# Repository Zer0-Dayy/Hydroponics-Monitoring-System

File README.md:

# Hydroponics Monitoring System

The [project handover](Project%20Handover/Source%20Code/HANDOVER.md) contains earlier source material for reference.

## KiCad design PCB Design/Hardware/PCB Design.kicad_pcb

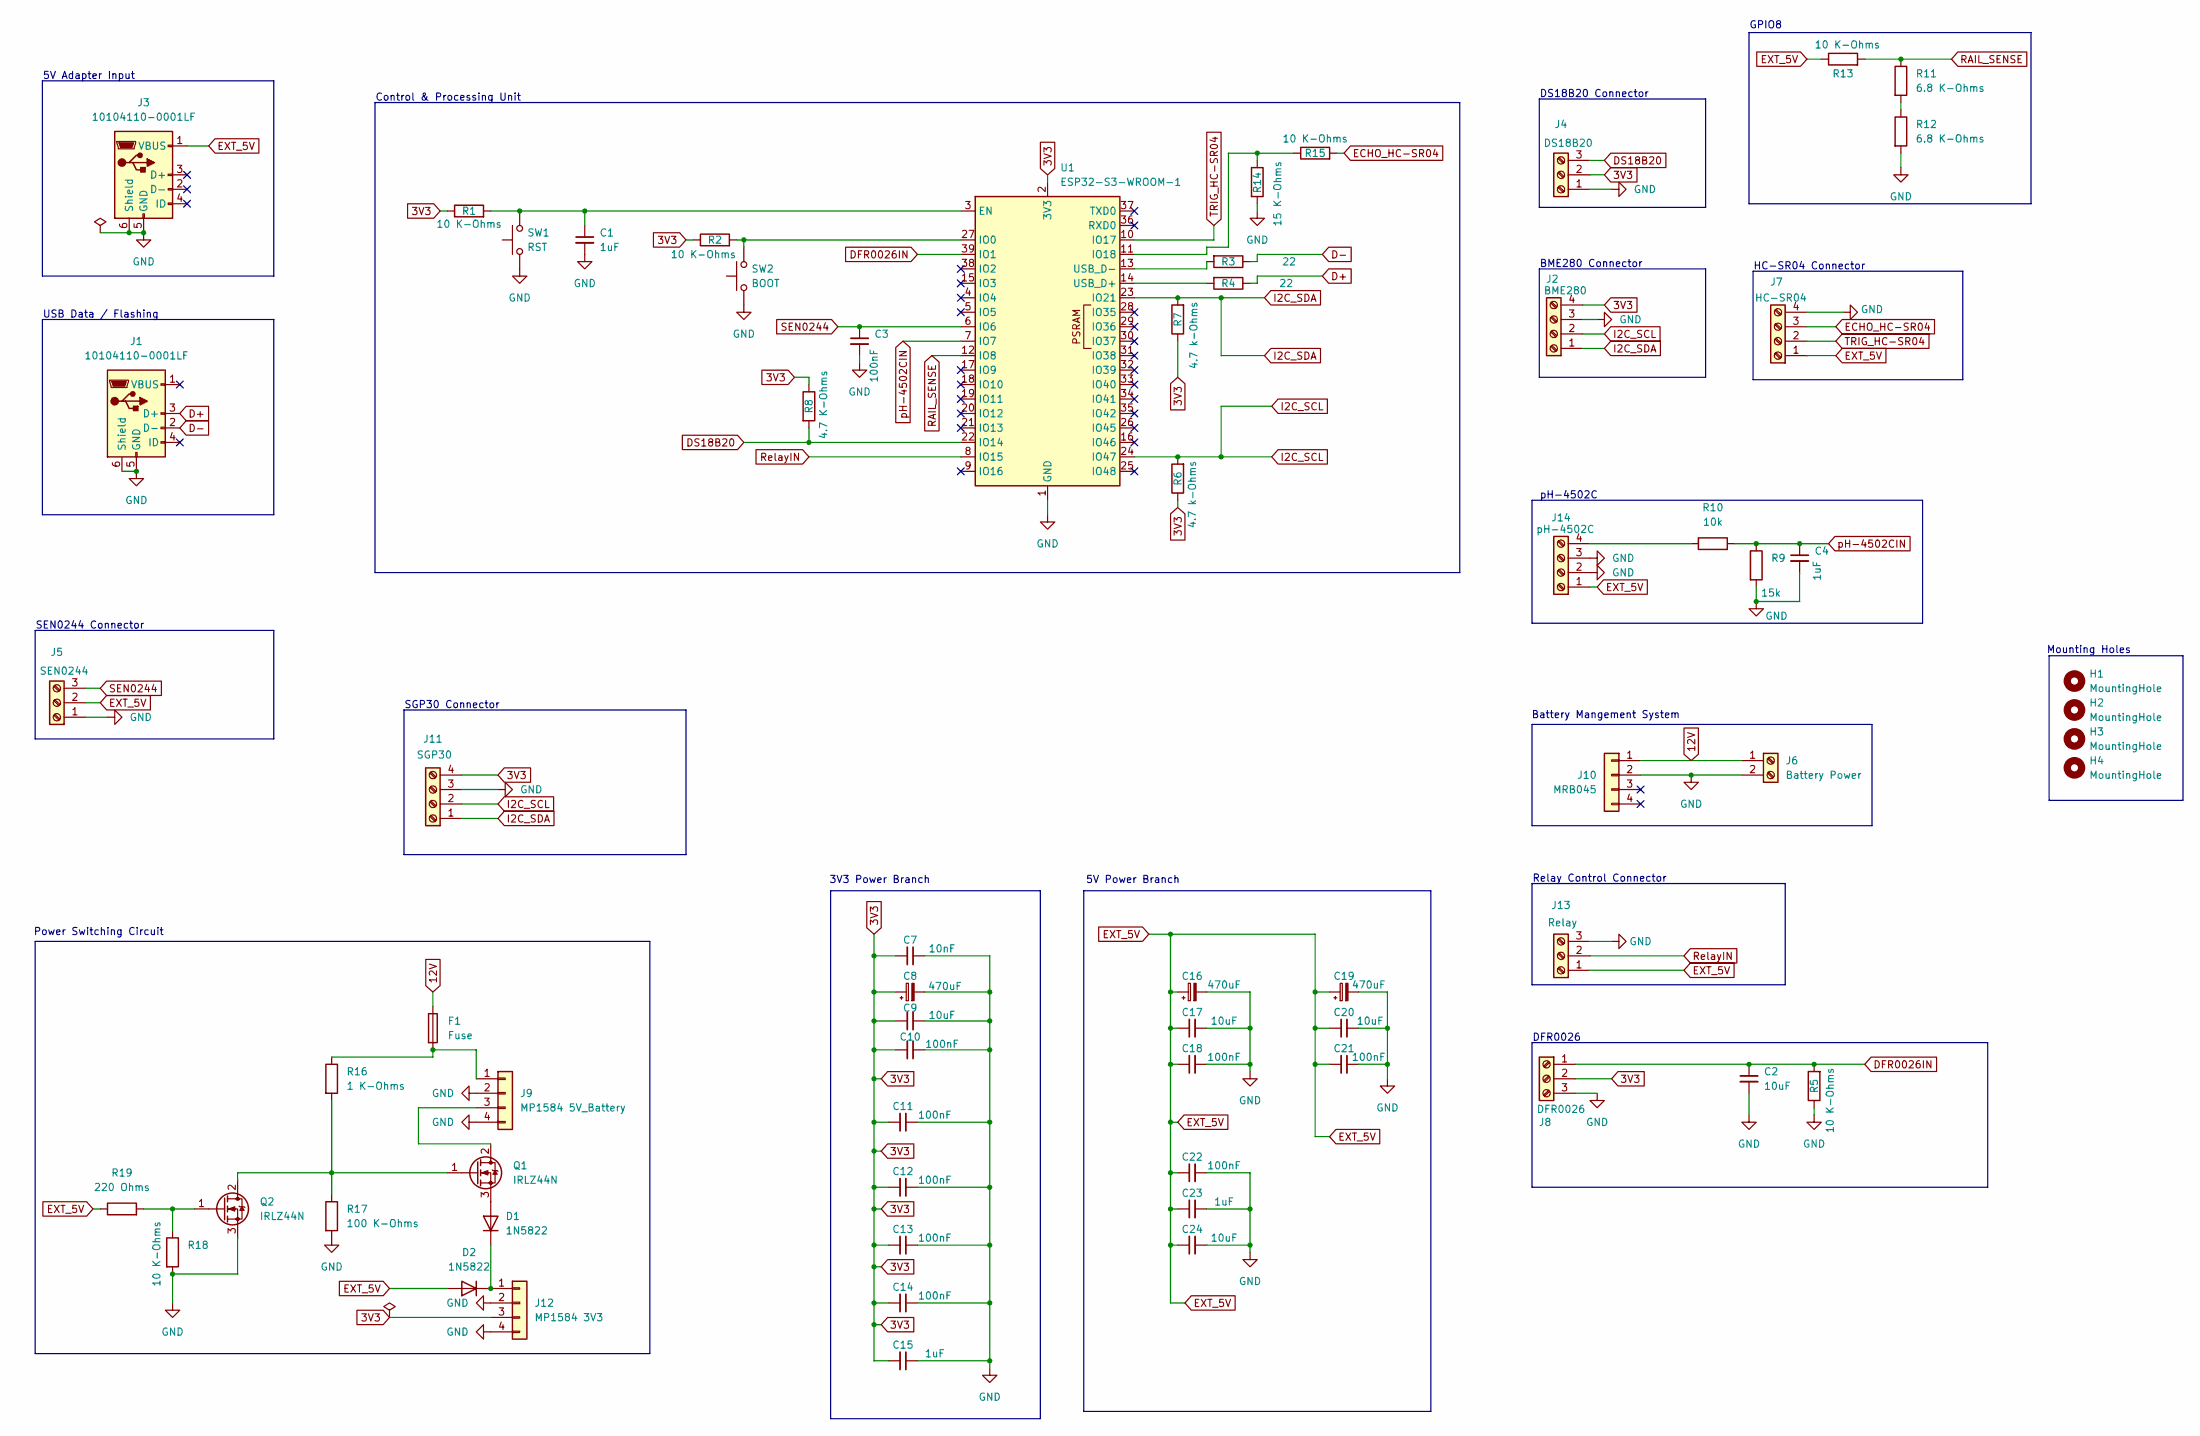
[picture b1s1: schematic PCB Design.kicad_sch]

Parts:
C1: 1uF; C_0402_1005Metric__C1
C2: 10uF; C_0805_2012Metric__C2
C3: 100nF; C_0805_2012Metric_Pad1.18x1.45mm_HandSolder__C3
C4: 1uF; C_0402_1005Metric__C4
C7: 10nF; C_0805_2012Metric__C7
C8: 470uF; CP_Radial_D5.0mm_P2.00mm__C8
C9: 10uF; C_0805_2012Metric__C9
C10: 100nF; C_0805_2012Metric__C10
C11: 100nF; C_0805_2012Metric__C11
C12: 100nF; C_0805_2012Metric__C12
C13: 100nF; C_0805_2012Metric__C13
C14: 100nF; C_0805_2012Metric__C14
C15: 1uF; C_0402_1005Metric__C15
C16: 470uF; CP_Radial_D5.0mm_P2.00mm__C16
C17: 10uF; C_0805_2012Metric__C17
C18: 100nF; C_0805_2012Metric__C18
C19: 470uF; CP_Radial_D5.0mm_P2.00mm__C19
C20: 10uF; C_0805_2012Metric__C20
C21: 100nF; C_0805_2012Metric__C21
C22: 100nF; C_0805_2012Metric__C22
C23: 1uF; C_0402_1005Metric__C23
C24: 10uF; C_0805_2012Metric__C24
D1: 1N5822; D_DO-201AD_P15.24mm_Horizontal__D1
D2: 1N5822; D_DO-201AD_P15.24mm_Horizontal__D2
F1: Fuse; Fuse_Littelfuse_395Series__F1
H1: MountingHole; MountingHole_3.2mm_M3__H1
H2: MountingHole; MountingHole_3.2mm_M3__H2
H3: MountingHole; MountingHole_3.2mm_M3__H3
H4: MountingHole; MountingHole_3.2mm_M3__H4
J1, J3: 10104110-0001LF; USB_Micro-B_Amphenol_10104110_Horizontal
J2: BME280; TerminalBlock_Phoenix_MKDS-1,5-4-5.08_1x04_P5.08mm_Horizont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
J4: DS18B20; TerminalBlock_Phoenix_MKDS-1,5-3-5.08_1x03_P5.08mm_Horizont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
J5: SEN0244; TerminalBlock_Phoenix_MKDS-1,5-3-5.08_1x03_P5.08mm_Horizont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
J6: Battery Power; TerminalBlock_Phoenix_MKDS-1,5-2-5.08_1x02_P5.08mm_Horizont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
J7: HC-SR04; TerminalBlock_Phoenix_MKDS-1,5-4-5.08_1x04_P5.08mm_Horizont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
J8: DFR0026; TerminalBlock_Phoenix_MKDS-1,5-3-5.08_1x03_P5.08mm_Horizont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
J9: MP1584 5V_Battery; MP1584EN_Module__J9
J10: MRB045; Charger_3S_TypeC_MRB045__J10
J11: SGP30; TerminalBlock_Phoenix_MKDS-1,5-4-5.08_1x04_P5.08mm_Horizont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
J12: MP1584 3V3; MP1584EN_Module__J12
J13: Relay; TerminalBlock_Phoenix_MKDS-1,5-3-5.08_1x03_P5.08mm_Horizont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
J14: pH-4502C; TerminalBlock_Phoenix_MKDS-1,5-4-5.08_1x04_P5.08mm_Horizont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
Q1: IRLZ44N; TO-220-3_Vertical__Q1
Q2: IRLZ44N; TO-220-3_Vertical__Q2
R1: 10 K-Ohms; R_0603_1608Metric__R1
R2: 10 K-Ohms; R_0603_1608Metric__R2
R3: 22; R_0603_1608Metric__R3
R4: 22; R_0603_1608Metric__R4
R5: 10 K-Ohms; R_0603_1608Metric__R5
R6: 4.7 k-Ohms; R_0603_1608Metric__R6
R7: 4.7 k-Ohms; R_0603_1608Metric__R7
R8: 4.7 K-Ohms; R_0603_1608Metric__R8
R9: 15k; R_0603_1608Metric__R9
R10: 10k; R_0603_1608Metric__R10
R11: 6.8 K-Ohms; R_0603_1608Metric__R11; Tolerance 1%
R12: 6.8 K-Ohms; R_0603_1608Metric__R12; Tolerance 1%
R13: 10 K-Ohms; R_0603_1608Metric__R13; Tolerance 1%
R14: 15 K-Ohms; R_0603_1608Metric__R14; Tolerance 1%
R15: 10 K-Ohms; R_0603_1608Metric__R15; Tolerance 1%
R16: 1 K-Ohms; R_1206_3216Metric__R16
R17: 100 K-Ohms; R_0603_1608Metric__R17
R18: 10 K-Ohms; R_0603_1608Metric__R18
R19: 220 Ohms; R_0603_1608Metric__R19
SW1: RST; SW_PUSH_6mm_H7.3mm__SW1
SW2: BOOT; SW_PUSH_6mm_H7.3mm__SW2
U1: ESP32-S3-WROOM-1; ESP32-S3-WROOM-1__U1

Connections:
3V3: C7.1, C8.1, C9.1, C10.1, C11.1, C12.1, C13.1, C14.1, C15.1, J2.4 (3V3), J4.2 (3V3), J8.2 (3V3), J11.4 (3V3), J12.3 (OUT+), R1.1, R2.1, R6.1, R7.1, R8.1, U1.2 (3V3)
12V: F1.1, J6.1, J10.1 (BAT+)
D+: J1.3 (D+), R4.1
D-: J1.2 (D-), R3.1
DFR0026IN: C2.1, J8.1 (SIGNAL), R5.2, U1.39 (IO1)
DS18B20: J4.3 (DQ), R8.2, U1.22 (IO14)
ECHO_HC-SR04: J7.3 (ECHO), R15.2
EXT_5V: C16.1, C17.1, C18.1, C19.1, C20.1, C21.1, C22.1, C23.1, C24.1, D2.2 (A), J3.1 (VBUS), J5.2 (3V3), J7.1 (5V), J13.1 (EXT_5V), J14.1 (EXT_5V), R13.1, R19.1
GND: C1.2, C2.2, C3.2, C4.2, C7.2, C8.2, C9.2, C10.2, C11.2, C12.2, C13.2, C14.2, C15.2, C16.2, C17.2, C18.2, C19.2, C20.2, C21.2, C22.2, C23.2, C24.2, J1.5 (GND), J1.6 (Shield), J2.3 (GND), J3.5 (GND), J3.6 (Shield), J4.1 (GND), J5.1 (GND), J6.2, J7.4 (GND), J8.3 (GND), J9.2 (IN-), J9.4 (OUT-), J10.2 (BAT-), J11.3 (GND), J12.2 (IN-), J12.4 (OUT-), J13.3 (GND), J14.2 (GND), J14.3 (GND), Q2.3 (S), R5.1, R9.2, R12.2, R14.2, R17.2, R18.2, SW1.1, SW2.1, U1.1 (GND), U1.40 (GND), U1.41 (GND)
I2C_SCL: J2.2 (SCL), J11.2 (SCL), R6.2, U1.24 (IO47)
I2C_SDA: J2.1 (SDA), J11.1 (SDA), R7.2, U1.23 (IO21)
unnamed: D1.2 (A), Q1.3 (S)
unnamed: D1.1 (K), D2.1 (K), J12.1 (IN+)
unnamed: F1.2, J9.1 (IN+), R16.1
unnamed: J9.3 (OUT+), Q1.2 (D)
unnamed: J14.4 (PO_ANALOG), R10.1
unnamed: Q1.1 (G), Q2.2 (D), R16.2, R17.1
unnamed: Q2.1 (G), R18.1, R19.2
unnamed: R11.2, R12.1
unnamed: C1.1, R1.2, SW1.2, U1.3 (EN)
unnamed: R2.2, SW2.2, U1.27 (IO0)
unnamed: R14.1, R15.1, U1.11 (IO18)
unnamed: R4.2, U1.14 (USB_D+)
unnamed: R3.2, U1.13 (USB_D-)
RAIL_SENSE: R11.1, R13.2, U1.12 (IO8)
RelayIN: J13.2 (RELAY_CTRL), U1.8 (IO15)
SEN0244: C3.1, J5.3 (AOUT), U1.6 (IO6)
TRIG_HC-SR04: J7.2 (TRIG), U1.10 (IO17)
pH-4502CIN: C4.1, R9.1, R10.2, U1.7 (IO7)

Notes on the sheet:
Control & Processing Unit
SEN0244 Connector
HC-SR04 Connector
3V3 Power Branch
SGP30 Connector
Power Switching Circuit
Mounting Holes
DFR0026
pH-4502C
BME280 Connector
Battery Mangement System
GPIO8
Relay Control Connector
DS18B20 Connector
5V Power Branch
USB Data / Flashing
5V Adapter Input

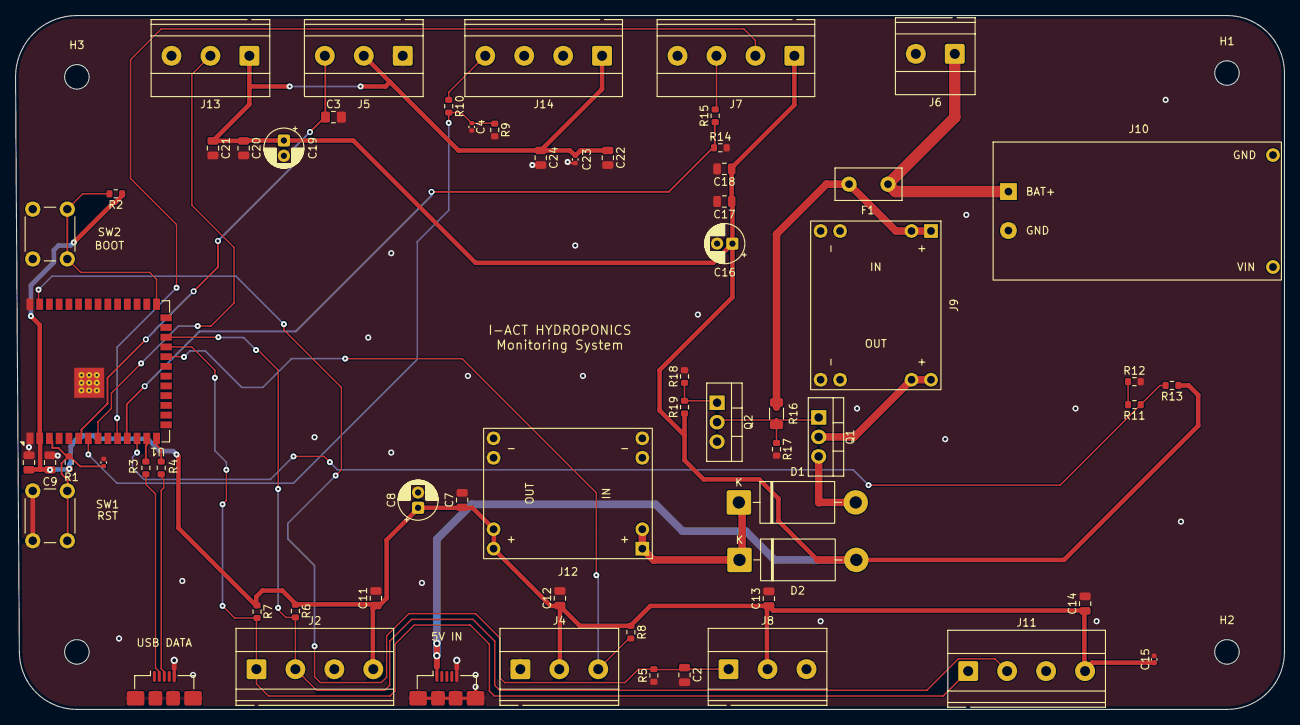
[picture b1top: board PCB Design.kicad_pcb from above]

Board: 2 copper layers, 165.5 x 90.5 mm, 67 parts (0 on the bottom side), 29 nets.

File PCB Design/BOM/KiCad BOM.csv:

"Reference","Value","Footprint","Qty","Tolerance","Power"
"C1","1uF","ProjectPCB:C_0402_1005Metric__C1","1","",""
"C2","10uF","ProjectPCB:C_0805_2012Metric__C2","1","",""
"C3","100nF","ProjectPCB:C_0805_2012Metric_Pad1.18x1.45mm_HandSolder__C3","1","",""
"C4","1uF","ProjectPCB:C_0402_1005Metric__C4","1","",""
"C7","10nF","ProjectPCB:C_0805_2012Metric__C7","1","",""
"C8","470uF","ProjectPCB:CP_Radial_D5.0mm_P2.00mm__C8","1","",""
"C9","10uF","ProjectPCB:C_0805_2012Metric__C9","1","",""
"C10","100nF","ProjectPCB:C_0805_2012Metric__C10","1","",""
"C11","100nF","ProjectPCB:C_0805_2012Metric__C11","1","",""
"C12","100nF","ProjectPCB:C_0805_2012Metric__C12","1","",""
"C13","100nF","ProjectPCB:C_0805_2012Metric__C13","1","",""
"C14","100nF","ProjectPCB:C_0805_2012Metric__C14","1","",""
"C15","1uF","ProjectPCB:C_0402_1005Metric__C15","1","",""
"C16","470uF","ProjectPCB:CP_Radial_D5.0mm_P2.00mm__C16","1","",""
"C17","10uF","ProjectPCB:C_0805_2012Metric__C17","1","",""
"C18","100nF","ProjectPCB:C_0805_2012Metric__C18","1","",""
"C19","470uF","ProjectPCB:CP_Radial_D5.0mm_P2.00mm__C19","1","",""
"C20","10uF","ProjectPCB:C_0805_2012Metric__C20","1","",""
"C21","100nF","ProjectPCB:C_0805_2012Metric__C21","1","",""
"C22","100nF","ProjectPCB:C_0805_2012Metric__C22","1","",""
"C23","1uF","ProjectPCB:C_0402_1005Metric__C23","1","",""
"C24","10uF","ProjectPCB:C_0805_2012Metric__C24","1","",""
"D1","1N5822","ProjectPCB:D_DO-201AD_P15.24mm_Horizontal__D1","1","",""
"D2","1N5822","ProjectPCB:D_DO-201AD_P15.24mm_Horizontal__D2","1","",""
"F1","Fuse","ProjectPCB:Fuse_Littelfuse_395Series__F1","1","",""
"J1","10104110-0001LF","ProjectPCB:USB_Micro-B_Amphenol_10104110_Horizontal","1","",""
"J2","BME280","ProjectPCB:TerminalBlock_Phoenix_MKDS-1,5-4-5.08_1x04_P5.08mm_Horizontal__J2","1","",""
"J3","10104110-0001LF","ProjectPCB:USB_Micro-B_Amphenol_10104110_Horizontal","1","",""
"J4","DS18B20","ProjectPCB:TerminalBlock_Phoenix_MKDS-1,5-3-5.08_1x03_P5.08mm_Horizontal__J4","1","",""
"J5","SEN0244","ProjectPCB:TerminalBlock_Phoenix_MKDS-1,5-3-5.08_1x03_P5.08mm_Horizontal__J5","1","",""
"J6","Battery Power","ProjectPCB:TerminalBlock_Phoenix_MKDS-1,5-2-5.08_1x02_P5.08mm_Horizontal__J6","1","",""
"J7","HC-SR04","ProjectPCB:TerminalBlock_Phoenix_MKDS-1,5-4-5.08_1x04_P5.08mm_Horizontal__J7","1","",""
"J8","DFR0026","ProjectPCB:TerminalBlock_Phoenix_MKDS-1,5-3-5.08_1x03_P5.08mm_Horizontal__J8","1","",""
"J9","MP1584 5V_Battery","ProjectPCB:MP1584EN_Module__J9","1","",""
"J10","MRB045","ProjectPCB:Charger_3S_TypeC_MRB045__J10","1","",""
"J11","SGP30","ProjectPCB:TerminalBlock_Phoenix_MKDS-1,5-4-5.08_1x04_P5.08mm_Horizontal__J11","1","",""
"J12","MP1584 3V3","ProjectPCB:MP1584EN_Module__J12","1","",""
"J13","Relay","ProjectPCB:TerminalBlock_Phoenix_MKDS-1,5-3-5.08_1x03_P5.08mm_Horizontal__J13","1","",""
"J14","pH-4502C","ProjectPCB:TerminalBlock_Phoenix_MKDS-1,5-4-5.08_1x04_P5.08mm_Horizontal__J14","1","",""
"Q1","IRLZ44N","ProjectPCB:TO-220-3_Vertical__Q1","1","",""
"Q2","IRLZ44N","ProjectPCB:TO-220-3_Vertical__Q2","1","",""
"R1","10 K-Ohms","ProjectPCB:R_0603_1608Metric__R1","1","",""
"R2","10 K-Ohms","ProjectPCB:R_0603_1608Metric__R2","1","",""
"R3","22","ProjectPCB:R_0603_1608Metric__R3","1","",""
"R4","22","ProjectPCB:R_0603_1608Metric__R4","1","",""
"R5","10k","ProjectPCB:R_0603_1608Metric__R5","1","",""
"R6","4.7 k-Ohms","ProjectPCB:R_0603_1608Metric__R6","1","",""
"R7","4.7 k-Ohms","ProjectPCB:R_0603_1608Metric__R7","1","",""
"R8","4.7 K-Ohms","ProjectPCB:R_0603_1608Metric__R8","1","",""
"R9","15k","ProjectPCB:R_0603_1608Metric__R9","1","",""
"R10","10k","ProjectPCB:R_0603_1608Metric__R10","1","",""
"R11","6.8k","ProjectPCB:R_0603_1608Metric__R11","1","1%",""
"R12","6.8k","ProjectPCB:R_0603_1608Metric__R12","1","1%",""
"R13","10k","ProjectPCB:R_0603_1608Metric__R13","1","1%",""
"R14","15k","ProjectPCB:R_0603_1608Metric__R14","1","1%",""
"R15","10k","ProjectPCB:R_0603_1608Metric__R15","1","1%",""
"R16","1 K-Ohms","ProjectPCB:R_1206_3216Metric__R16","1","","0.25W minimum"
"R17","100 K-Ohms","ProjectPCB:R_0603_1608Metric__R17","1","",""
"R18","10 K-Ohms","ProjectPCB:R_0603_1608Metric__R18","1","",""
"R19","220 Ohms","ProjectPCB:R_0603_1608Metric__R19","1","",""
"SW1","RST","ProjectPCB:SW_PUSH_6mm_H7.3mm__SW1","1","",""
"SW2","BOOT","ProjectPCB:SW_PUSH_6mm_H7.3mm__SW2","1","",""
"U1","ESP32-S3-WROOM-1","ProjectPCB:ESP32-S3-WROOM-1__U1","1","",""
